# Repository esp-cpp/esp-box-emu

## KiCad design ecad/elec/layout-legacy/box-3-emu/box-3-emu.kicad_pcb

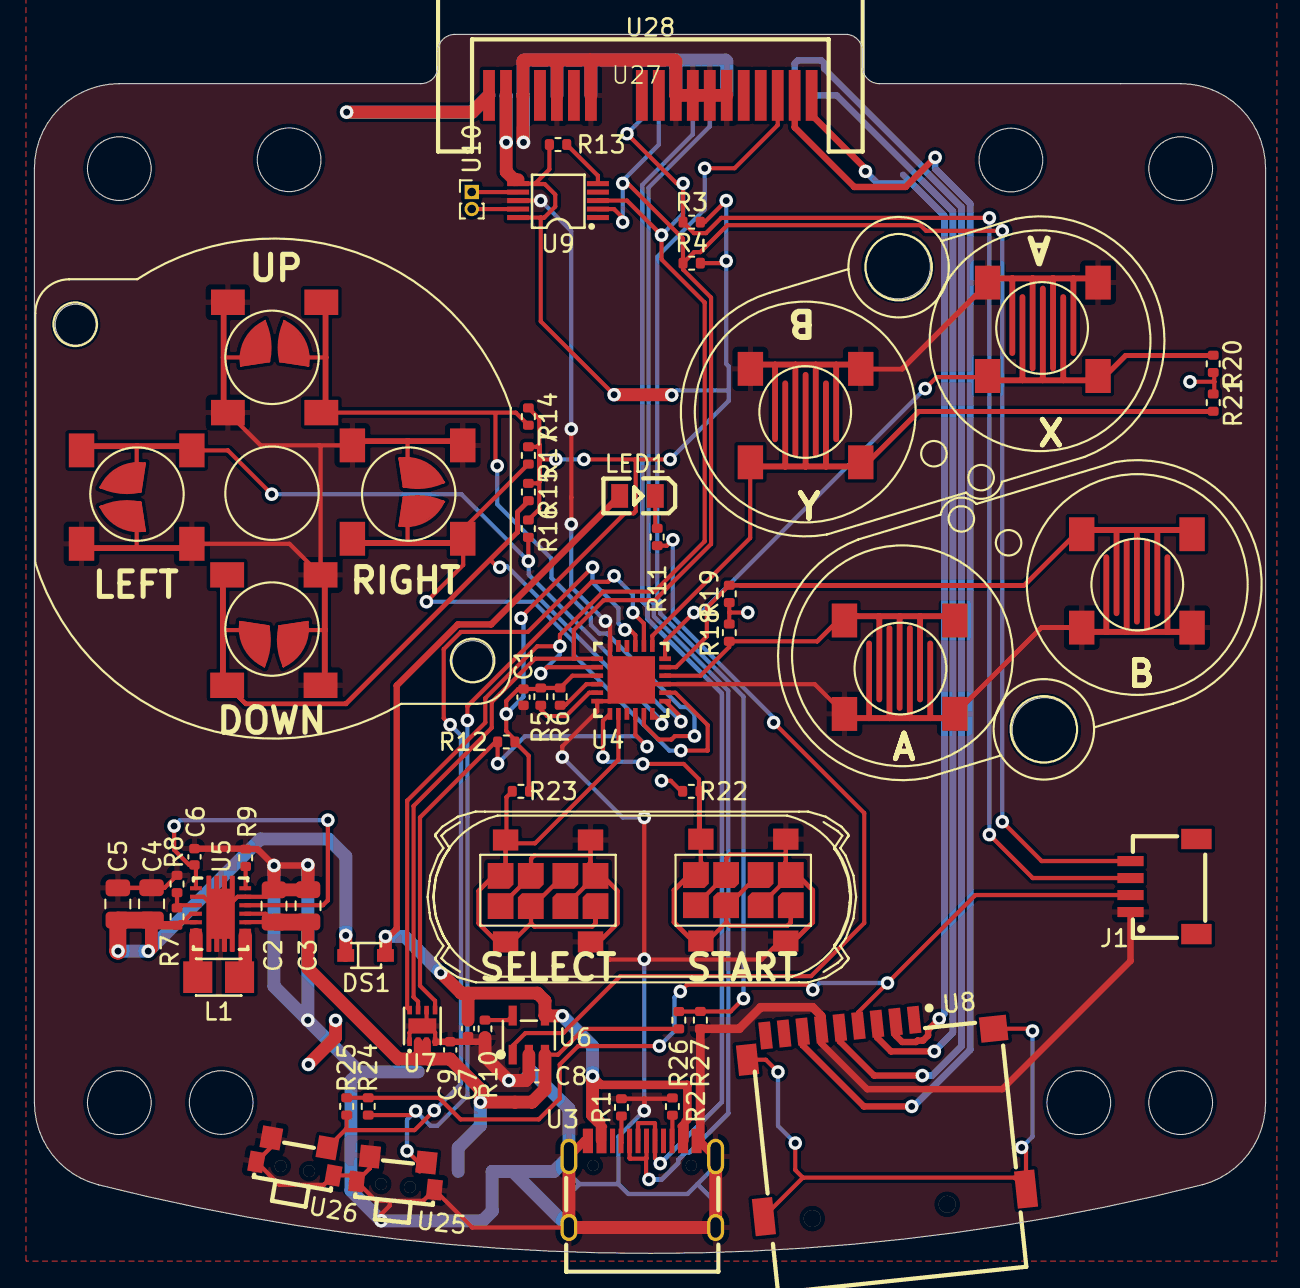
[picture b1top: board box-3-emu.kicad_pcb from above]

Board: 2 copper layers, 72.5 x 71.8 mm, 68 parts (1 on the bottom side), 42 nets.

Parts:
C1, C6, C9: 16V 100nF X7R ±10% 0402 Multilayer Ceramic Capaci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; C0402
C2, C3, C4, C5: 25V 10uF X5R ±10% 0805 Multilayer Ceramic Capacit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; C0805
C7, C8: 10V 4.7uF X5R ±20% 0402 Multilayer Ceramic Capaci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; C0402
DS1: SOD-323_L1.8-W1.3-LS2.5-RD
J1: CONN-SMD_4P-P1.00_SM04B-SRSS-TB-LF-SN
L1: IND-SMD_L2.5-W2.0_WPN252012H
LED1: LED0805-R-RD
R1, R2: 62.5mW Thick Film Resistors 50V ±100ppm/℃ ±1% 4.7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; R0402
R3, R4, R5, R6, R12, R13, R14, R15, R16, R17, R18, R19, R20, R21, R22, R23, R24, R25: 62.5mW Thick Film Resistors 50V ±100ppm/℃ ±1% 10k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; R0402
R7: 62.5mW Thick Film Resistors ±100ppm/℃ ±1% 243kΩ 0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; R0402
R8: 62.5mW Thick Film Resistors 50V ±100ppm/℃ ±1% 27.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; R0402
R9: 62.5mW Thick Film Resistors 50V ±100ppm/℃ ±1% 1MΩ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; R0402
R10: 62.5mW Thick Film Resistors 50V ±100ppm/℃ ±1% 2kΩ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; R0402
R11: 62.5mW Thick Film Resistors 50V ±100ppm/℃ ±1% 2.5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; R0402
R26: 62.5mW Thick Film Resistors 50V ±100ppm/℃ ±1% 255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; R0402
R27: 62.5mW Thick Film Resistors 50V ±100ppm/℃ ±1% 249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; R0402
U1: BOX_EMU_BASE
U2: CONN-SMD_P2.00_S2B-PH-SM4-TB-LF-SN
U3: USB-C-SMD_TYPE-611-T3-W
U4: VFQFPN-24_L4.0-W4.0-P0.50-BL-EP2.8
U5: VSON-14_L4.0-W3.0-P0.50-BL-EP_TI_DSJ
U6: SOT-23-5_L3.0-W1.7-P0.95-LS2.8-BL
U7: DFN-8_L2.0-W2.0-P0.50-BL-EP
U8: SIM-SMD_C9900007362
U9: VSSOP-10_L3.0-W3.0-P0.50-LS4.9-BL
U10: PinHeader_1x02_P1.00mm_Vertical
U11: GAMEBOY_COLOR_DPAD_MEMBRANE
U12, U13, U14, U15: GBC_DPAD_BUTTON
U16, U19: GAMEBOY_COLOR_A_B_BUTTON_MEMBRANE
U17, U18, U20, U21: GBC_A_B_BUTTON
U22: GAMEBOY_COLOR_START_SELECT_MEMBRANE
U23, U24: GBC_START_SELECT_BUTTON
U25, U26: SW-SMD_TS24CA
U27: BOX_3_EMU
U28: CONN-SMD_5-1734857-1

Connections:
battery_measurement: R26.2, R27.1, U28.A3
box-gnd: C1.2, C2.2, C3.2, C4.2, C5.2, C6.2, C7.2, C8.2, C9.2, J1.1, R1.2, R2.2, R8.2, R9.2, R10.2, R27.2, U2.2, U2.3, U2.4, U3.17, U3.18, U3.19, U3.20, U3.A1, U3.A12, U3.B1, U3.B12, U4.9, U4.18, U4.24, U4.25, U5.2, U5.13, U5.15, U6.2, U7.1, U7.4, U7.6, U7.9, U8.6, U9.8, U12.2, U12.4, U13.2, U13.4, U14.2, U14.4, U15.2, U15.4, U17.2, U17.4, U18.2, U18.4, U20.2, U20.4, U21.2, U21.4, U23.2, U23.4, U24.2, U24.4, U25.2, U25.3, U25.4, U26.2, U26.3, U26.4, U28.A6, U28.A7, U28.A8, U28.A9, U28.A12, U28.A14, U28.A16, U28.B6, U28.B9, U28.B12, U28.B14, U28.B16
box.drv2605.chip-a: U9.7, U10.1
box.drv2605.chip-b: U9.9, U10.2
box.io-a: R18.2, U4.10, U17.1, U17.3
box.io-b: R19.2, U4.11, U18.1, U18.3
box.mcp73831-gnd: R11.2, U6.1
cathode: LED1.2, R11.1
cc1: R1.1, U3.A5
cc2: R2.1, U3.B5
cs: U8.2, U28.A1
dm: U3.A7, U3.B7, U28.B7
down: R15.2, U4.6, U13.1, U13.3
dp: U3.A6, U3.B6, U28.B8
en: R13.1, U9.5
intn: R6.2, U4.22
l1: L1.1, U5.8, U5.9
l2: L1.2, U5.6, U5.7
left: R16.2, U4.7, U14.1, U14.3
miso: U8.7, U28.A2
mosi: U8.3, U28.B1
out: R7.2, R8.1, U5.3
p1_3: R12.1, U4.4, U7.5
pg: R9.1, U5.14
prog: R10.1, U6.5
right: R17.2, U4.8, U15.1, U15.3
rstn: R5.2, U4.23
sck: U8.5, U28.B2
scl: J1.4, R4.1, U4.19, U7.7, U9.2, U28.B10
sda: J1.3, R3.1, U4.20, U7.8, U9.3, U28.B11
select: R23.2, U4.2, U24.1, U24.3
start: R22.2, U4.1, U23.1, U23.3
up: R14.2, U4.5, U12.1, U12.3
vbat: C2.1, C3.1, C8.1, C9.1, R26.1, U2.1, U5.10, U5.11, U6.3, U7.2, U7.3
vbus: C7.1, DS1.2, LED1.1, U3.A4, U3.A9, U3.B4, U3.B9, U6.4
vcc_3v3: C1.1, J1.2, R3.2, R4.2, R5.1, R6.1, R12.2, R13.2, R14.1, R15.1, R16.1, R17.1, R18.1, R19.1, R20.1, R21.1, R22.1, R23.1, R24.1, R25.1, U4.21, U8.4, U9.6, U9.10, U28.A17, U28.B17
vcc_5v: C4.1, C5.1, DS1.1, R7.1, U5.4, U5.5, U28.A18, U28.B18
vina: C6.1, U5.1, U5.12
vol_down: R25.2, U4.15, U26.1
vol_up: R24.2, U4.14, U25.1
x: R20.2, U4.12, U20.1, U20.3
y: R21.2, U4.13, U21.1, U21.3

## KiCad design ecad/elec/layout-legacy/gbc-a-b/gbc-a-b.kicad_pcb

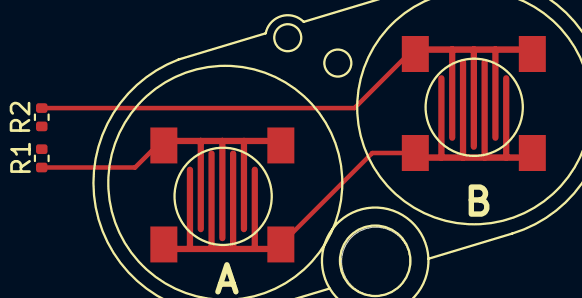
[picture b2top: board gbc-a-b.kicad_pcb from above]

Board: 2 copper layers, 5 parts (0 on the bottom side), 4 nets.

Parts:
R1, R2: 62.5mW Thick Film Resistors 50V ±100ppm/℃ ±1% 10k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; R0402
U1: GAMEBOY_COLOR_A_B_BUTTON_MEMBRANE
U2, U3: GBC_A_B_BUTTON

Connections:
a: R1.2, U2.1, U2.3
b: R2.2, U3.1, U3.3
gnd: U2.2, U2.4, U3.2, U3.4
vcc: R1.1, R2.1
